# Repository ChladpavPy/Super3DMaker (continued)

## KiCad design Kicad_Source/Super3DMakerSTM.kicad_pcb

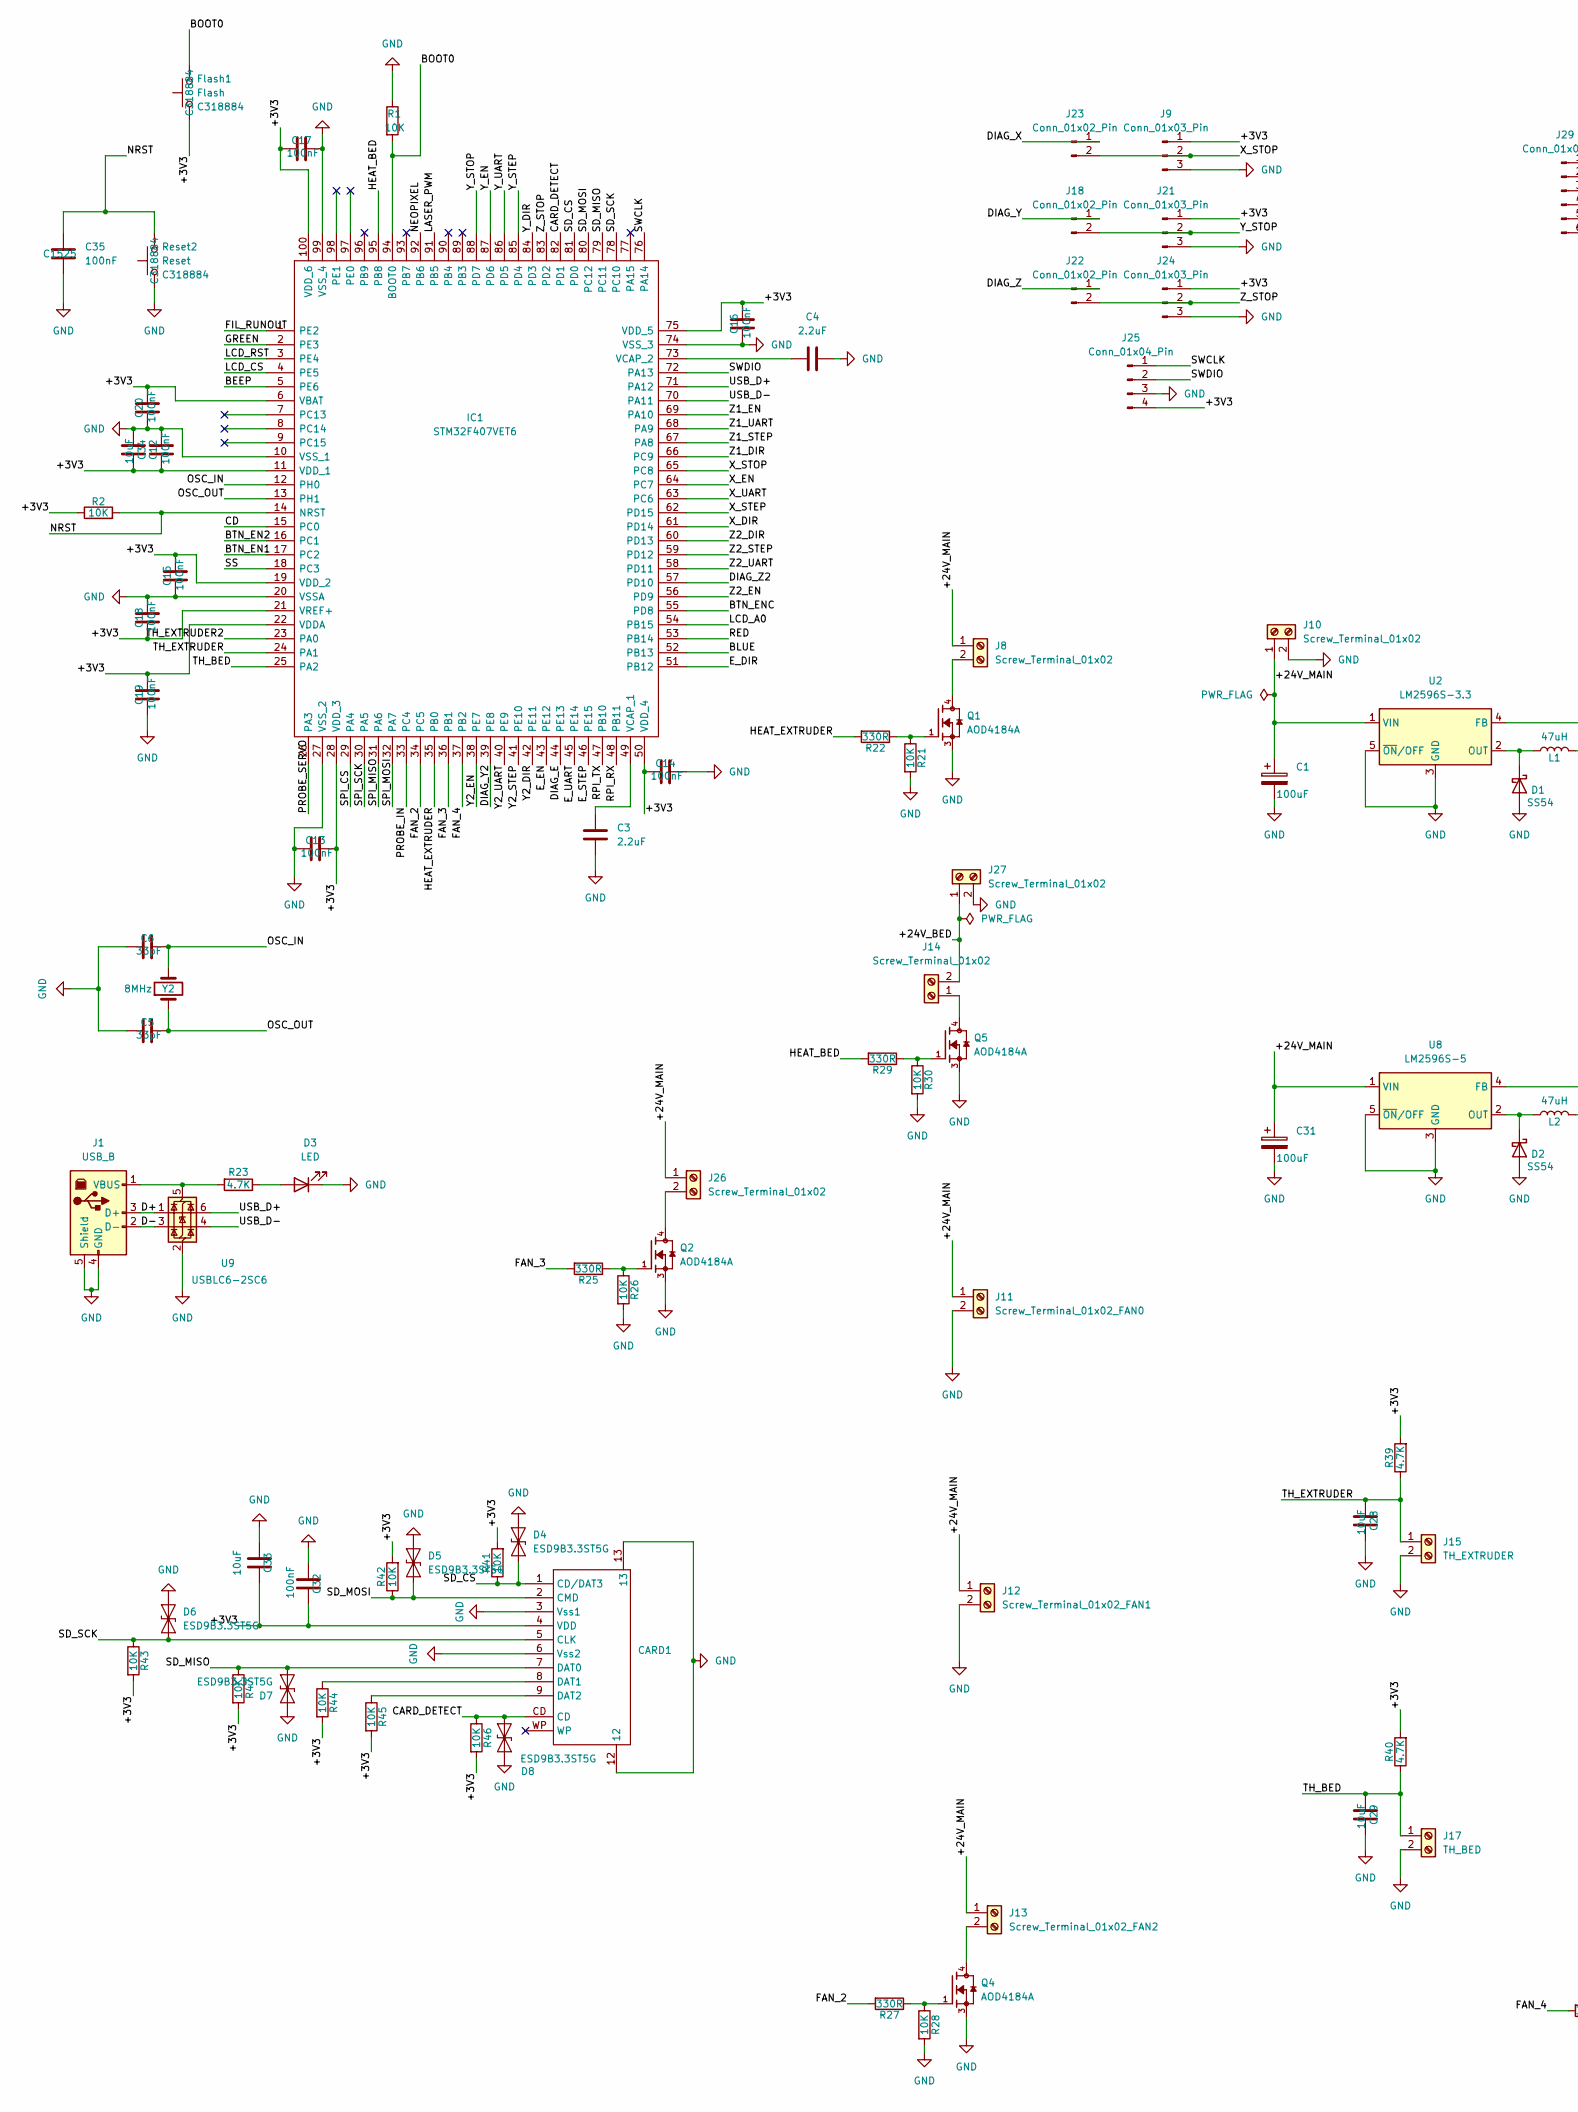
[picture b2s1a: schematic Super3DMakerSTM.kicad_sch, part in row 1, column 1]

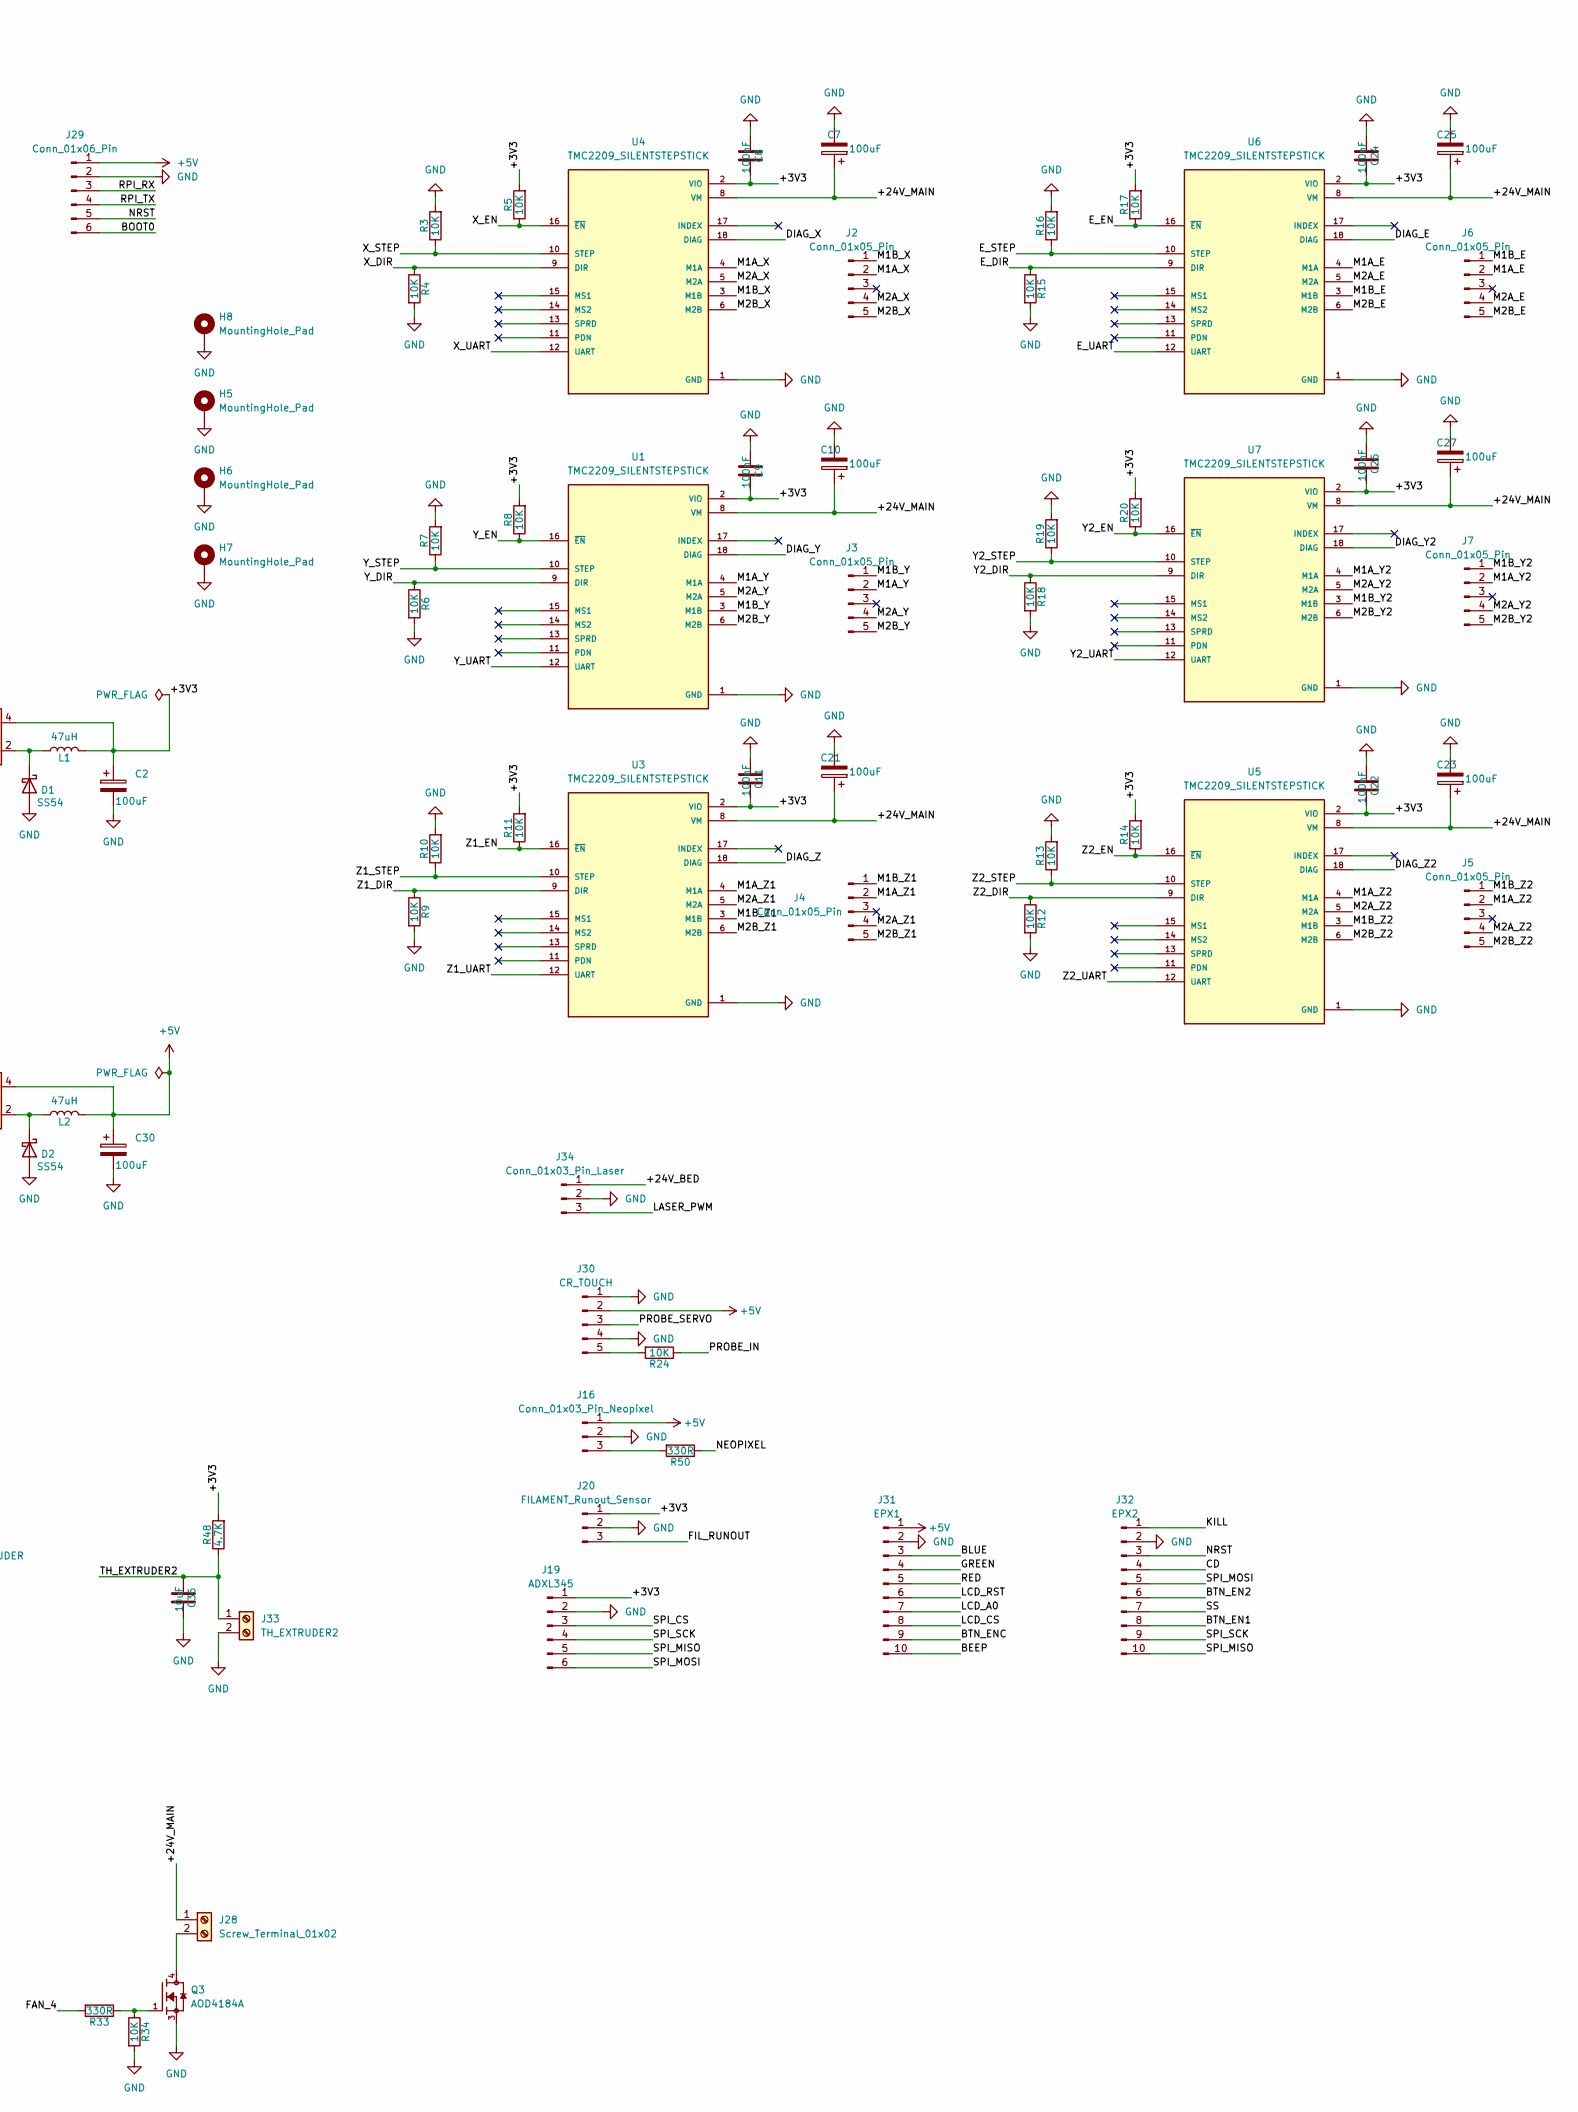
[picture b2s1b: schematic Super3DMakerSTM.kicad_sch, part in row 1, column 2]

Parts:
C1, C2, C7, C10, C21, C23, C25, C27, C30, C31: 100uF; CP_Elec_6.3x7.7; LCSC C3352
C3, C4: 2.2uF; C_0603_1608Metric; LCSC C23630
C5, C6: 33pF; C_0402_1005Metric; LCSC C1562
C8, C9, C11, C22, C24, C26: 100nF; C_0603_1608Metric; LCSC C14663
C12, C13, C14, C15, C16, C17, C18, C19, C20: 100nF; C_0402_1005Metric; LCSC C307331
C28, C29, C36: 10uF; C_0603_1608Metric; LCSC C14663
C32: 100nF; C_0402_1005Metric; LCSC C14663
C33: 10uF; C_0603_1608Metric; LCSC C19702
C34: 10uF; C_0805_2012Metric; LCSC C14663
C35: 100nF; C_0402_1005Metric; MNF PART NUMBER C1525; LCSC C1525
CARD1: SD_KARTA_OPRAVENA; Manufacturer Part SD-006M; LCSC Part Name 自弹式 标准SD卡 卡座
D1, D2: SS54; D_SMA; LCSC C22452
D3: LED; LED0603-RD; LCSC C2286
D4, D5, D6, D7, D8: ESD9B3.3ST5G; D_SOD-923; LCSC C96512
Flash1: Flash; SW_Push_1P1T_XKB_TS-1187A; MNF PART NUMBER C318884; LCSC C318884
H5, H6, H7, H8: MountingHole_Pad; MountingHole_3.2mm_M3_Pad_Via
IC1: STM32F407VET6; LQFP100-0.5-13.8X13.8MM; Manufacturer_Part_Number STM32F407VET6; Mouser Part Number 511-STM32F407VET6
J1: USB_B; USB_B_OST_USB-B1HSxx_Horizontal; LCSC C498173
J2, J3, J4, J5, J6, J7: Conn_01x05_Pin; Molex_KK-254_AE-6410-05A_1x05_P2.54mm_Vertical
J8, J26, J28: Screw_Terminal_01x02; Molex_KK-254_AE-6410-02A_1x02_P2.54mm_Vertical
J9, J21, J24: Conn_01x03_Pin; Molex_KK-254_AE-6410-03A_1x03_P2.54mm_Vertical
J10, J14, J27: Screw_Terminal_01x02; TerminalBlock_Phoenix_MKDS-1,5-2-5.08_1x02_P5.08mm_Horizont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
J11: Screw_Terminal_01x02_FAN0; Molex_KK-254_AE-6410-02A_1x02_P2.54mm_Vertical
J12: Screw_Terminal_01x02_FAN1; Molex_KK-254_AE-6410-02A_1x02_P2.54mm_Vertical
J13: Screw_Terminal_01x02_FAN2; Molex_KK-254_AE-6410-02A_1x02_P2.54mm_Vertical
J15: TH_EXTRUDER; Molex_KK-254_AE-6410-02A_1x02_P2.54mm_Vertical
J16: Conn_01x03_Pin_Neopixel; Molex_KK-254_AE-6410-03A_1x03_P2.54mm_Vertical
J17: TH_BED; Molex_KK-254_AE-6410-02A_1x02_P2.54mm_Vertical
J18, J22, J23: Conn_01x02_Pin; PinHeader_1x02_P2.54mm_Vertical
J19: ADXL345; Molex_KK-254_AE-6410-06A_1x06_P2.54mm_Vertical
J20: FILAMENT_Runout_Sensor; Molex_KK-254_AE-6410-03A_1x03_P2.54mm_Vertical
J25: Conn_01x04_Pin; PinHeader_1x04_P2.54mm_Vertical
J29: Conn_01x06_Pin; PinHeader_1x06_P2.54mm_Vertical
J30: CR_TOUCH; PinHeader_1x05_P2.54mm_Vertical
J31: EPX1; IDC-Header_2x05_P2.54mm_Vertical
J32: EPX2; IDC-Header_2x05_P2.54mm_Vertical
J33: TH_EXTRUDER2; Molex_KK-254_AE-6410-02A_1x02_P2.54mm_Vertical
J34: Conn_01x03_Pin_Laser; Molex_KK-254_AE-6410-03A_1x03_P2.54mm_Vertical
L1, L2: 47uH; IND-SMD_L12.3-W12.3; MNF PART NUMBER C9906; LCSC C9906
Q1, Q2, Q3, Q4, Q5: AOD4184A; DPAK228P994X240-4N; PARTREV 0; LCSC C99124
R1, R2, R24, R41, R42, R43, R44, R45, R46, R47: 10K; R_0402_1005Metric; LCSC C25804
R3, R4, R5, R6, R7, R8, R9, R10, R11, R12, R13, R14, R15, R16, R17, R18, R19, R20, R21, R26, R28, R30, R34: 10K; R_0603_1608Metric; LCSC C25804
R22, R25, R27, R29, R33, R50: 330R; R_0402_1005Metric; LCSC C25104
R23: 4.7K; R_0805_2012Metric; LCSC C17673
R39, R40, R48: 4.7K; R_0402_1005Metric; LCSC C25900
Reset2: Reset; SW_Push_1P1T_XKB_TS-1187A; MNF PART NUMBER C318884; LCSC C318884
U1, U3, U4, U5, U6, U7: TMC2209_SILENTSTEPSTICK; MODULE_TMC2209_SILENTSTEPSTICK; PARTREV 1.20
U2: LM2596S-3.3; TO-263-5_TabPin3; LCSC C42421958
U8: LM2596S-5; TO-263-5_TabPin3; LCSC C42421959
U9: USBLC6-2SC6; SOT-23-6; LCSC C7519
Y2: 8MHz; Crystal_SMD_5032-2Pin_5.0x3.2mm; LCSC C115962

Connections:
+5V: C30.1, J16.1, J29.1, J30.2, J31.1, L2.2, U8.4 (FB)
/+3V3: C2.1, C8.1, C9.1, C11.1, C12.2, C13.1, C14.2, C15.1, C16.1, C17.2, C18.2, C19.1, C20.1, C22.1, C24.1, C26.1, C32.1, C33.1, C34.1, CARD1.4 (VDD), Flash1.1, IC1.6 (VBAT), IC1.11 (VDD_1), IC1.19 (VDD_2), IC1.21 (VREF+), IC1.22 (VDDA), IC1.28 (VDD_3), IC1.50 (VDD_4), IC1.75 (VDD_5), IC1.100 (VDD_6), J9.1, J19.1, J20.1, J21.1, J24.1, J25.4, L1.2, R2.1, R5.2, R8.2, R11.2, R14.2, R17.2, R20.2, R39.2, R40.2, R41.2, R42.2, R43.2, R44.2, R45.2, R46.2, R47.2, R48.2, U1.2 (VIO), U2.4 (FB), U3.2 (VIO), U4.2 (VIO), U5.2 (VIO), U6.2 (VIO), U7.2 (VIO)
/+24V_BED: J14.2, J27.1, J34.1
/+24V_MAIN: C1.1, C7.1, C10.1, C21.1, C23.1, C25.1, C27.1, C31.1, J8.1, J10.1, J11.1, J12.1, J13.1, J26.1, J28.1, U1.8 (VM), U2.1 (VIN), U3.8 (VM), U4.8 (VM), U5.8 (VM), U6.8 (VM), U7.8 (VM), U8.1 (VIN)
/BEEP: IC1.5 (PE6), J31.10
/BLUE: IC1.52 (PB13), J31.3
/BOOT0: Flash1.2, IC1.94 (BOOT0), J29.6, R1.2
/BTN_EN1: IC1.17 (PC2), J32.8
/BTN_EN2: IC1.16 (PC1), J32.6
/BTN_ENC: IC1.55 (PD8), J31.9
/CARD_DETECT: CARD1.CD, D8.2 (A2), IC1.82 (PD1), R46.1
/CD: IC1.15 (PC0), J32.4
/D+: J1.3 (D+), U9.1 (I/O1)
/D-: J1.2 (D-), U9.3 (I/O2)
/DIAG_E: IC1.44 (PE13), U6.18 (DIAG)
/DIAG_X: J23.1, U4.18 (DIAG)
/DIAG_Y: J18.1, U1.18 (DIAG)
/DIAG_Y2: IC1.39 (PE8), U7.18 (DIAG)
/DIAG_Z: J22.1, U3.18 (DIAG)
/DIAG_Z2: IC1.57 (PD10), U5.18 (DIAG)
/E_DIR: IC1.51 (PB12), R15.1, U6.9 (DIR)
/E_EN: IC1.43 (PE12), R17.1, U6.16 (~EN)
/E_STEP: IC1.46 (PE15), R16.1, U6.10 (STEP)
/E_UART: IC1.45 (PE14), U6.12 (UART)
/FAN_2: IC1.34 (PC5), R27.2
/FAN_3: IC1.36 (PB1), R25.2
/FAN_4: IC1.37 (PB2), R33.2
/FIL_RUNOUT: IC1.1 (PE2), J20.3
/GREEN: IC1.2 (PE3), J31.4
/HEAT_BED: IC1.95 (PB8), R29.2
/HEAT_EXTRUDER: IC1.35 (PB0), R22.2
/KILL: J32.1
/LASER_PWM: IC1.91 (PB5), J34.3
/LCD_A0: IC1.54 (PB15), J31.7
/LCD_CS: IC1.4 (PE5), J31.8
/LCD_RST: IC1.3 (PE4), J31.6
/M1A_E: J6.2, U6.4 (M1A)
/M1A_X: J2.2, U4.4 (M1A)
/M1A_Y: J3.2, U1.4 (M1A)
/M1A_Y2: J7.2, U7.4 (M1A)
/M1A_Z1: J4.2, U3.4 (M1A)
/M1A_Z2: J5.2, U5.4 (M1A)
/M1B_E: J6.1, U6.3 (M1B)
/M1B_X: J2.1, U4.3 (M1B)
/M1B_Y: J3.1, U1.3 (M1B)
/M1B_Y2: J7.1, U7.3 (M1B)
/M1B_Z1: J4.1, U3.3 (M1B)
/M1B_Z2: J5.1, U5.3 (M1B)
/M2A_E: J6.4, U6.5 (M2A)
/M2A_X: J2.4, U4.5 (M2A)
/M2A_Y: J3.4, U1.5 (M2A)
/M2A_Y2: J7.4, U7.5 (M2A)
/M2A_Z1: J4.4, U3.5 (M2A)
/M2A_Z2: J5.4, U5.5 (M2A)
/M2B_E: J6.5, U6.6 (M2B)
/M2B_X: J2.5, U4.6 (M2B)
/M2B_Y: J3.5, U1.6 (M2B)
/M2B_Y2: J7.5, U7.6 (M2B)
/M2B_Z1: J4.5, U3.6 (M2B)
/M2B_Z2: J5.5, U5.6 (M2B)
/NEOPIXEL: IC1.92 (PB6), R50.1
/NRST: C35.1, IC1.14 (NRST), J29.5, J32.3, R2.2, Reset2.2
/OSC_IN: C6.1, IC1.12 (PH0), Y2.2
/OSC_OUT: C5.1, IC1.13 (PH1), Y2.1
/PROBE_IN: IC1.33 (PC4), R24.1
/PROBE_SERVO: IC1.26 (PA3), J30.3
/RED: IC1.53 (PB14), J31.5
/RPI_RX: IC1.48 (PB11), J29.3
/RPI_TX: IC1.47 (PB10), J29.4
/SD_CS: CARD1.1 (CD/DAT3), D4.2 (A2), IC1.81 (PD0), R41.1
/SD_MISO: CARD1.7 (DAT0), D7.2 (A2), IC1.79 (PC11), R47.1
/SD_MOSI: CARD1.2 (CMD), D5.2 (A2), IC1.80 (PC12), R42.1
/SD_SCK: CARD1.5 (CLK), D6.2 (A2), IC1.78 (PC10), R43.1
/SPI_CS: IC1.29 (PA4), J19.3
/SPI_MISO: IC1.31 (PA6), J19.5, J32.10
/SPI_MOSI: IC1.32 (PA7), J19.6, J32.5
/SPI_SCK: IC1.30 (PA5), J19.4, J32.9
/SS: IC1.18 (PC3), J32.7
/SWCLK: IC1.76 (PA14), J25.1
/SWDIO: IC1.72 (PA13), J25.2
/TH_BED: C29.2, IC1.25 (PA2), J17.1, R40.1
/TH_EXTRUDER: C28.2, IC1.24 (PA1), J15.1, R39.1
/TH_EXTRUDER2: C36.2, IC1.23 (PA0), J33.1, R48.1
/USB_D+: IC1.71 (PA12), U9.6 (I/O1)
/USB_D-: IC1.70 (PA11), U9.4 (I/O2)
/X_DIR: IC1.61 (PD14), R4.1, U4.9 (DIR)
/X_EN: IC1.64 (PC7), R5.1, U4.16 (~EN)
/X_STEP: IC1.62 (PD15), R3.1, U4.10 (STEP)
/X_STOP: IC1.65 (PC8), J9.2, J23.2
/X_UART: IC1.63 (PC6), U4.12 (UART)
/Y2_DIR: IC1.42 (PE11), R18.1, U7.9 (DIR)
/Y2_EN: IC1.38 (PE7), R20.1, U7.16 (~EN)
/Y2_STEP: IC1.41 (PE10), R19.1, U7.10 (STEP)
/Y2_UART: IC1.40 (PE9), U7.12 (UART)
/Y_DIR: IC1.84 (PD3), R6.1, U1.9 (DIR)
/Y_EN: IC1.87 (PD6), R8.1, U1.16 (~EN)
/Y_STEP: IC1.85 (PD4), R7.1, U1.10 (STEP)
/Y_STOP: IC1.88 (PD7), J18.2, J21.2
/Y_UART: IC1.86 (PD5), U1.12 (UART)
/Z1_DIR: IC1.66 (PC9), R9.1, U3.9 (DIR)
/Z1_EN: IC1.69 (PA10), R11.1, U3.16 (~EN)
/Z1_STEP: IC1.67 (PA8), R10.1, U3.10 (STEP)
/Z1_UART: IC1.68 (PA9), U3.12 (UART)
/Z2_DIR: IC1.60 (PD13), R12.1, U5.9 (DIR)
/Z2_EN: IC1.56 (PD9), R14.1, U5.16 (~EN)
/Z2_STEP: IC1.59 (PD12), R13.1, U5.10 (STEP)
/Z2_UART: IC1.58 (PD11), U5.12 (UART)
/Z_STOP: IC1.83 (PD2), J22.2, J24.2
GND: C1.2, C2.2, C3.1, C4.2, C5.2, C6.2, C7.2, C8.2, C9.2, C10.2, C11.2, C12.1, C13.2, C14.1, C15.2, C16.2, C17.1, C18.1, C19.2, C20.2, C21.2, C22.2, C23.2, C24.2, C25.2, C26.2, C27.2, C28.1, C29.1, C30.2, C31.2, C32.2, C33.2, C34.2, C35.2, C36.1, CARD1.3 (Vss1), CARD1.6 (Vss2), CARD1.12, CARD1.13, D1.2 (A), D2.2 (A), D3.1 (K), D4.1 (A1), D5.1 (A1), D6.1 (A1), D7.1 (A1), D8.1 (A1), H5.1 (1_1), H6.1 (1_1), H7.1 (1_1), H8.1 (1_1), IC1.10 (VSS_1), IC1.20 (VSSA), IC1.27 (VSS_2), IC1.74 (VSS_3), IC1.99 (VSS_4), J1.4 (GND), J1.5 (Shield), J9.3, J10.2, J11.2, J12.2, J15.2, J16.2, J17.2, J19.2, J20.2, J21.3, J24.3, J25.3, J27.2, J29.2, J30.1, J30.4, J31.2, J32.2, J33.2, J34.2, Q1.3, Q2.3, Q3.3, Q4.3, Q5.3, R1.1, R3.2, R4.2, R6.2, R7.2, R9.2, R10.2, R12.2, R13.2, R15.2, R16.2, R18.2, R19.2, R21.2, R26.2, R28.2, R30.2, R34.2, Reset2.1, U1.1 (GND), U1.7 (GND), U2.3 (GND), U2.5 (~ON/OFF), U3.1 (GND), U3.7 (GND), U4.1 (GND), U4.7 (GND), U5.1 (GND), U5.7 (GND), U6.1 (GND), U6.7 (GND), U7.1 (GND), U7.7 (GND), U8.3 (GND), U8.5 (~ON/OFF), U9.2 (GND)
unnamed: CARD1.8 (DAT1), R44.1
unnamed: CARD1.9 (DAT2), R45.1
unnamed: D1.1 (K), L1.1, U2.2 (OUT)
unnamed: D2.1 (K), L2.1, U8.2 (OUT)
unnamed: D3.2 (A), R23.1
unnamed: C3.2, IC1.49 (VCAP_1)
unnamed: C4.1, IC1.73 (VCAP_2)
unnamed: J1.1 (VBUS), R23.2, U9.5 (VBUS)
unnamed: J8.2, Q1.4
unnamed: J13.2, Q4.4
unnamed: J14.1, Q5.4
unnamed: J16.3, R50.2
unnamed: J26.2, Q2.4
unnamed: J28.2, Q3.4
unnamed: J30.5, R24.2
unnamed: Q1.1, R21.1, R22.1
unnamed: Q2.1, R25.1, R26.1
unnamed: Q3.1, R33.1, R34.1
unnamed: Q4.1, R27.1, R28.1
unnamed: Q5.1, R29.1, R30.1

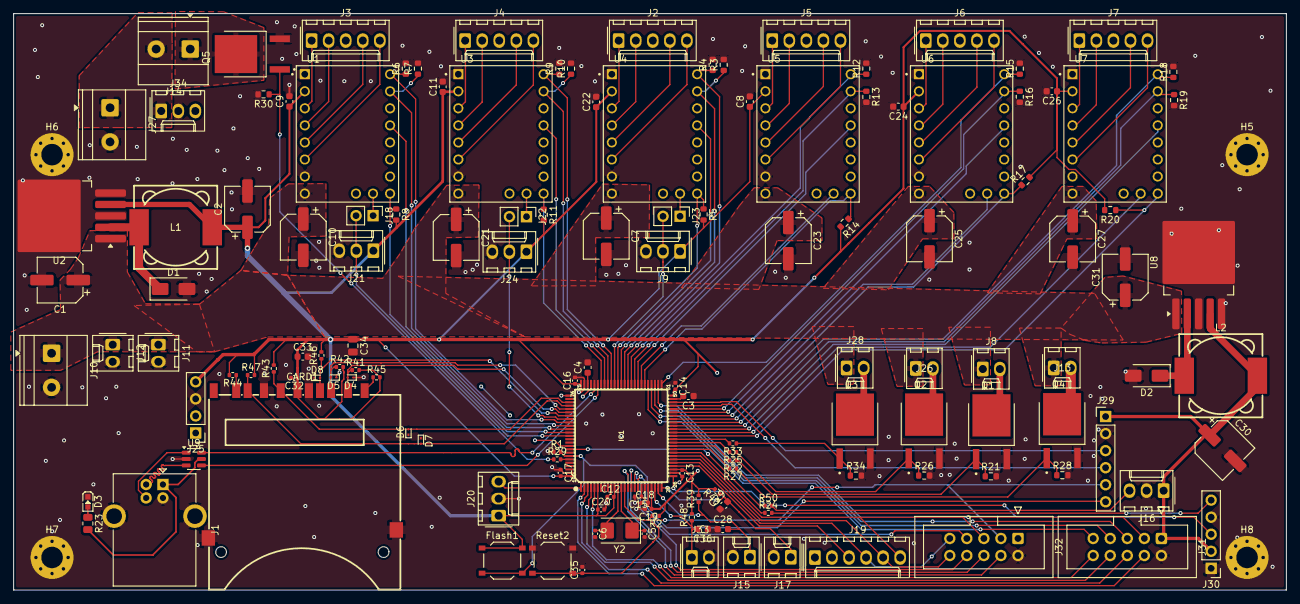
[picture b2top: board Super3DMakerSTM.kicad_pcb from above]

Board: 4 copper layers, 189.6 x 85.9 mm, 146 parts (0 on the bottom side), 128 nets.

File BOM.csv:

Reference,Qty,Value,DNP,Exclude from BOM,Exclude from Board,Footprint,Datasheet,MNF PART NUMBER,LCSC
"C1,C2,C7,C10,C21,C23,C25,C27,C30,C31",10,100uF,,,,Capacitor_SMD:CP_Elec_6.3x7.7,,C3352,C3352
"C3,C4",2,2.2uF,,,,Capacitor_SMD:C_0603_1608Metric,,C23630,C23630
"C5,C6",2,33pF,,,,Capacitor_SMD:C_0402_1005Metric,,C1562,C1562
"C8,C9,C11,C22,C24,C26",6,100nF,,,,Capacitor_SMD:C_0603_1608Metric,,C14663,C14663
"C12,C13,C14,C15,C16,C17,C18,C19,C20",9,100nF,,,,Capacitor_SMD:C_0402_1005Metric,,C307331,C307331
"C28,C29,C36",3,10uF,,,,Capacitor_SMD:C_0603_1608Metric,,C14663,C14663
C32,1,100nF,,,,Capacitor_SMD:C_0402_1005Metric,,C14663,C14663
C33,1,10uF,,,,Capacitor_SMD:C_0603_1608Metric,,C19702,C19702
C34,1,10uF,,,,Capacitor_SMD:C_0805_2012Metric,,C14663,C14663
C35,1,100nF,,,,Capacitor_SMD:C_0402_1005Metric,,C1525,C1525
CARD1,1,SD_CARD,,,,Moje_knihovna:SD_KARTA_OPRAVENA,https://item.szlcsc.com/datasheet/SD-006M/136893.html,C125615,C125615
"D1,D2",2,SS54,,,,Diode_SMD:D_SMA,,C22452,C22452
D3,1,LED,,,,LED_SMD:LED0603-RD,,C2286,C2286
"D4,D5,D6,D7,D8",5,ESD9B3.3ST5G,,,,Diode_SMD:D_SOD-923,https://www.onsemi.com/pub/Collateral/ESD9B-D.PDF,C96512,C96512
Flash1,1,Flash,,,,Button_Switch_SMD:SW_Push_1P1T_XKB_TS-1187A,,C318884,C318884
IC1,1,STM32F407VET6,,,,Moje_knihovna:LQFP100-0.5-13.8X13.8MM,https://www.st.com/resource/en/datasheet/stm32f405zg.pdf,C28730,C28730
J1,1,USB_B,,,,Connector_USB:USB_B_OST_USB-B1HSxx_Horizontal,,C498173,C498173
"J2,J3,J4,J5,J6,J7",6,Conn_01x05_Pin,,,,Connector_Molex:Molex_KK-254_AE-6410-05A_1x05_P2.54mm_Vertical,,,
"J8,J26,J28",3,Screw_Terminal_01x02,,,,Connector_Molex:Molex_KK-254_AE-6410-02A_1x02_P2.54mm_Vertical,,,
"J9,J21,J24",3,Conn_01x03_Pin,,,,Connector_Molex:Molex_KK-254_AE-6410-03A_1x03_P2.54mm_Vertical,,,
"J10,J14,J27",3,Screw_Terminal_01x02,,,,TerminalBlock_Phoenix:TerminalBlock_Phoenix_MKDS-1,5-2-5.08_1x02_P5.08mm_Horizontal,,,
J11,1,Screw_Terminal_01x02_FAN0,,,,Connector_Molex:Molex_KK-254_AE-6410-02A_1x02_P2.54mm_Vertical,,,
J12,1,Screw_Terminal_01x02_FAN1,,,,Connector_Molex:Molex_KK-254_AE-6410-02A_1x02_P2.54mm_Vertical,,,
J13,1,Screw_Terminal_01x02_FAN2,,,,Connector_Molex:Molex_KK-254_AE-6410-02A_1x02_P2.54mm_Vertical,,,
J15,1,TH_EXTRUDER,,,,Connector_Molex:Molex_KK-254_AE-6410-02A_1x02_P2.54mm_Vertical,,,
J16,1,Conn_01x03_Pin_Neopixel,,,,Connector_Molex:Molex_KK-254_AE-6410-03A_1x03_P2.54mm_Vertical,,,
J17,1,TH_BED,,,,Connector_Molex:Molex_KK-254_AE-6410-02A_1x02_P2.54mm_Vertical,,,
"J18,J22,J23",3,Conn_01x02_Pin,,,,Connector_PinHeader_2.54mm:PinHeader_1x02_P2.54mm_Vertical,,,
J19,1,ADXL345,,,,Connector_Molex:Molex_KK-254_AE-6410-06A_1x06_P2.54mm_Vertical,,,
J20,1,FILAMENT_Runout_Sensor,,,,Connector_Molex:Molex_KK-254_AE-6410-03A_1x03_P2.54mm_Vertical,,,
J25,1,Conn_01x04_Pin,,,,Connector_PinHeader_2.54mm:PinHeader_1x04_P2.54mm_Vertical,,,
J29,1,Conn_01x06_Pin,,,,Connector_PinHeader_2.54mm:PinHeader_1x06_P2.54mm_Vertical,,,
J30,1,CR_TOUCH,,,,Connector_PinHeader_2.54mm:PinHeader_1x05_P2.54mm_Vertical,,,
J31,1,EPX1,,,,Connector_IDC:IDC-Header_2x05_P2.54mm_Vertical,,,
J32,1,EPX2,,,,Connector_IDC:IDC-Header_2x05_P2.54mm_Vertical,,,
J33,1,TH_EXTRUDER2,,,,Connector_Molex:Molex_KK-254_AE-6410-02A_1x02_P2.54mm_Vertical,,,
J34,1,Conn_01x03_Pin_Laser,,,,Connector_Molex:Molex_KK-254_AE-6410-03A_1x03_P2.54mm_Vertical,,,
"L1,L2",2,47uH,,,,Inductor_SMD:IND-SMD_L12.3-W12.3,,C9906,C9906
"Q1,Q2,Q3,Q4,Q5",5,AOD4184A,,,,Moje_knihovna:DPAK228P994X240-4N,,C99124,C99124
"R1,R2,R24,R41,R42,R43,R44,R45,R46,R47",10,10K,,,,Resistor_SMD:R_0402_1005Metric,,C25804,C25804
"R3,R4,R5,R6,R7,R8,R9,R10,R11,R12,R13,R14,R15,R16,R17,R18,R19,R20,R21,R26,R28,R30,R34",23,10K,,,,Resistor_SMD:R_0603_1608Metric,,C25804,C25804
"R22,R25,R27,R29,R33,R50",6,330R,,,,Resistor_SMD:R_0402_1005Metric,,C25104,C25104
R23,1,4.7K,,,,Resistor_SMD:R_0805_2012Metric,,C17673,C17673
"R39,R40,R48",3,4.7K,,,,Resistor_SMD:R_0402_1005Metric,,C25900,C25900
Reset2,1,Reset,,,,Button_Switch_SMD:SW_Push_1P1T_XKB_TS-1187A,,C318884,C318884
"U1,U3,U4,U5,U6,U7",6,TMC2209_SILENTSTEPSTICK,,,,Moje_knihovna:MODULE_TMC2209_SILENTSTEPSTICK,,,
U2,1,LM2596S-3.3,,,,Package_TO_SOT_SMD:TO-263-5_TabPin3,http://www.ti.com/lit/ds/symlink/lm2596.pdf,C42421958,C42421958
U8,1,LM2596S-5,,,,Package_TO_SOT_SMD:TO-263-5_TabPin3,http://www.ti.com/lit/ds/symlink/lm2596.pdf,C42421959,C42421959
U9,1,USBLC6-2SC6,,,,Package_TO_SOT_SMD:SOT-23-6,https://www.st.com/resource/en/datasheet/usblc6-2.pdf,C7519,C7519
Y2,1,8MHz,,,,Crystal:Crystal_SMD_5032-2Pin_5.0x3.2mm,,C115962,C115962
"H5,H6,H7,H8",4,MountingHole,,,,MountingHole_3.2mm_M3_Pad_Via,,,

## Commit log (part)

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2026-05-12 Rename project from Hack3DMaker to Super3DMaker
2026-05-17 Enhance README with project details and BOM
    Expanded project description and added detailed features, BOM, and assembly information.
2026-05-17 Create Firmware
2026-05-17 Rename Snímek obrazovky 2026-05-17 124707.png to schematics.png
2026-05-17 Rename Snímek obrazovky 2026-05-17 125100.png to pcb_b.png
2026-05-17 Rename Snímek obrazovky 2026-05-17 125039.png to pcb_f.png
2026-05-17 Rename Snímek obrazovky 2026-05-17 125022.png to pcb_in1.png
2026-05-17 Rename Snímek obrazovky 2026-05-17 124927.png to pcb_in2.png
2026-05-17 Rename Snímek obrazovky 2026-05-17 124850.png to pcb_b22.png
2026-05-17 Rename pcb_b22.png to pcb_b2.png
2026-05-17 Rename Snímek obrazovky 2026-05-17 124820.png to pcb_f2.png
2026-05-17 Update images in the README gallery section
2026-05-17 Rename Super3DMakerSTM.csv to BOM.csv
2026-05-17 Update README with KiCad version and klipper details
    Updated KiCad version from 8 to 10 and corrected 'klipper' capitalization.
2026-05-17 Enhance README with project explanation and formatting
    Added project background and details about reverse-engineering the old board. Updated section headers and improved formatting.
